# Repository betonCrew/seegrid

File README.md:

seegrid
================================
a floating lighting installation

# Electronics

* nRF24L01+ (2.4GHz)
* xmc1100
* AL8860
* 47µF inductor
* cree rgbw led

## LED

# Mechanics

# Firmware

# Software

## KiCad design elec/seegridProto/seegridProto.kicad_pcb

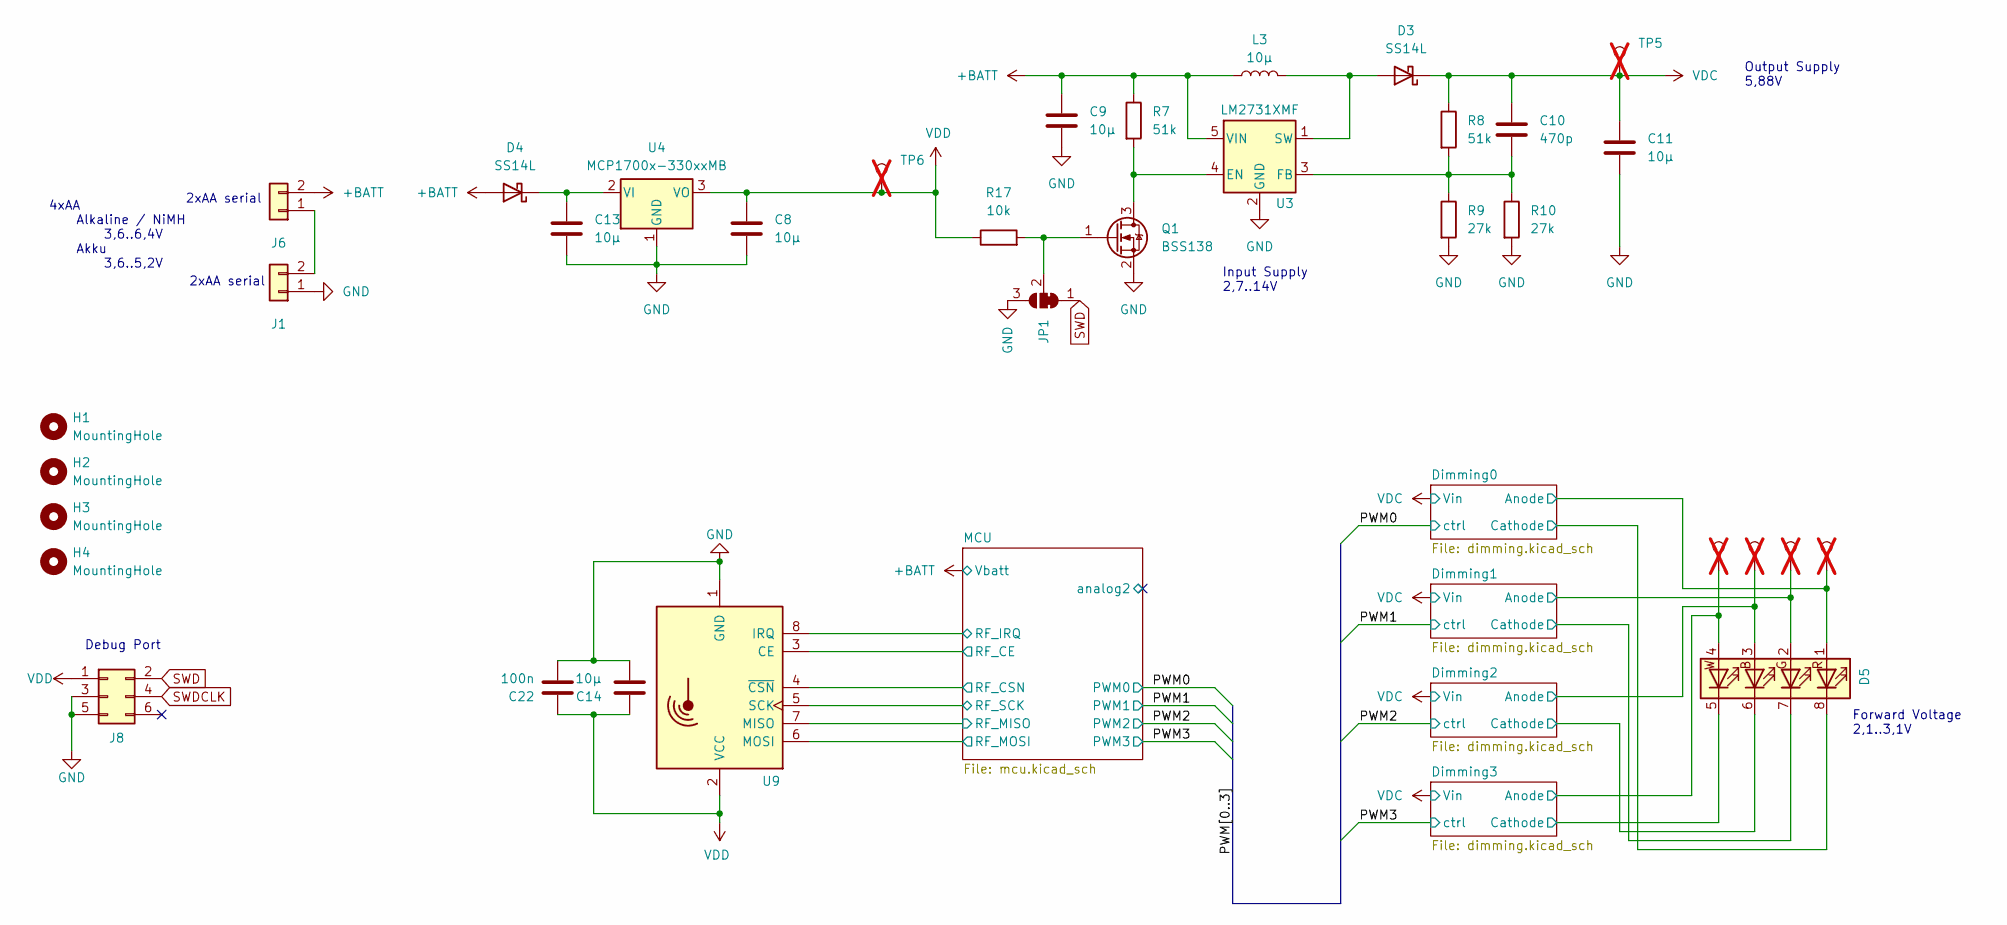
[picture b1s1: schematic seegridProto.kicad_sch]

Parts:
C8, C9, C11, C13, C14: 10µ; C_0603_1608Metric
C10: 470p; C_0603_1608Metric
C22: 100n; C_0603_1608Metric
D3, D4: SS14L; SOD-123FL
D5: CLQ6B-TKW-S1L1R1H1TBB7935AA3; Cree_PLCC8
H1, H2, H3, H4: MountingHole; MountingHole_3.2mm_M3
J1, J6: Conn_01x02; PinSocket_1x02_P2.54mm_Vertical
J8: Conn_02x04_Odd_Even; Tag-Connect_TC2030-IDC-NL_2x03_P1.27mm_Vertical
JP1: SolderJumper_3_Bridged12; SolderJumper-3_P1.3mm_Bridged12_RoundedPad1.0x1.5mm
L3: 10µ; L_7.3x7.3_H4.5
Q1: BSS138; SOT-23
R7, R8: 51k; R_0603_1608Metric
R9, R10: 27k; R_0603_1608Metric
R17: 10k; R_0603_1608Metric
TP1, TP2, TP3, TP4, TP5, TP6: TestPoint; TestPoint_Pad_D1.0mm; not fitted
U3: LM2731XMF; SOT-23-5
U4: MCP1700x-330xxMB; SOT-89-3
U9: NRF24L01_Breakout; nRF24L01_Breakout

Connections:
+BATT: C9.1, D4.2 (A), J6.2, L3.1, R7.1, U3.5 (VIN); also elsewhere on the board
/Dimming0/Anode: D5.1 (RK), TP1.1; also elsewhere on the board
/Dimming0/Cathode: D5.8 (RA); also elsewhere on the board
/Dimming1/Anode: D5.2 (GK), TP2.1; also elsewhere on the board
/Dimming1/Cathode: D5.7 (GA); also elsewhere on the board
/Dimming2/Anode: D5.3 (BK), TP3.1; also elsewhere on the board
/Dimming2/Cathode: D5.6 (BA); also elsewhere on the board
/Dimming3/Anode: D5.4 (BK), TP4.1; also elsewhere on the board
/Dimming3/Cathode: D5.5 (BA); also elsewhere on the board
/MCU/RF_CE: U9.3 (CE); also elsewhere on the board
/MCU/RF_CSN: U9.4 (~CSN); also elsewhere on the board
/MCU/RF_IRQ: U9.8 (IRQ); also elsewhere on the board
/MCU/RF_MISO: U9.7 (MISO); also elsewhere on the board
/MCU/RF_MOSI: U9.6 (MOSI); also elsewhere on the board
/MCU/RF_SCK: U9.5 (SCK); also elsewhere on the board
GND: C8.2, C9.2, C11.2, C13.2, C14.2, C22.2, J1.1, J8.3, J8.5, JP1.3 (B), Q1.2 (S), R9.2, R10.2, U3.2 (GND), U4.1 (GND), U9.1 (GND); also elsewhere on the board
unnamed: D3.2 (A), L3.2, U3.1 (SW)
unnamed: C13.1, D4.1 (K), U4.2 (VI)
unnamed: J1.2, J6.1
unnamed: JP1.2 (C), Q1.1 (G), R17.2
unnamed: Q1.3 (D), R7.2, U3.4 (EN)
unnamed: C10.2, R8.2, R9.1, R10.1, U3.3 (FB)
SWD: J8.2, JP1.1 (A); also elsewhere on the board
SWDCLK: J8.4; also elsewhere on the board
VDC: C10.1, C11.1, D3.1 (K), R8.1, TP5.1; also elsewhere on the board
VDD: C8.1, C14.1, C22.1, J8.1, R17.1, TP6.1, U4.3 (VO), U9.2 (VCC); also elsewhere on the board

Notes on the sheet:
Debug Port
Input Supply 2,7..14V
Forward Voltage 2,1..3,1V
Output Supply 5,88V
2xAA serial
4xAA Alkaline / NiMH 3,6..6,4V Akku 3,6..5,2V

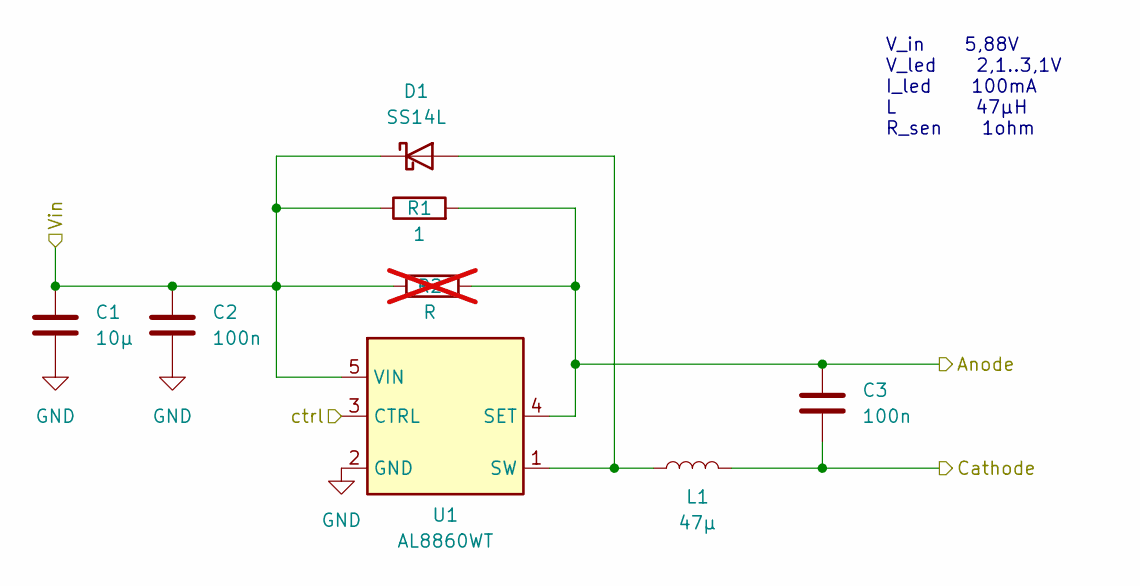
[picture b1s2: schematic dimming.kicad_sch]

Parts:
C1: 10µ; C_0603_1608Metric
C2, C3: 100n; C_0603_1608Metric
D1: SS14L; SOD-123FL
L1: 47µ; L_7.3x7.3_H4.5
R1: 1; R_0603_1608Metric
R2: R; R_0603_1608Metric; not fitted
U1: AL8860WT; TSOT-23-5

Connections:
/Dimming0/Anode: C3.1, R1.2, R2.2, U1.4 (SET); also elsewhere on the board
/Dimming0/Cathode: C3.2, L1.2; also elsewhere on the board
/PWM0: U1.3 (CTRL); also elsewhere on the board
GND: C1.2, C2.2, U1.2 (GND); also elsewhere on the board
unnamed: D1.2 (A), L1.1, U1.1 (SW)
VDC: C1.1, C2.1, D1.1 (K), R1.1, R2.1, U1.5 (VIN); also elsewhere on the board

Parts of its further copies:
C4, C16, C19: 10µ; C_0603_1608Metric
C5, C6, C17, C18, C20, C21: 100n; C_0603_1608Metric
D2, D6, D7: SS14L; SOD-123FL
L2, L4, L5: 47µ; L_7.3x7.3_H4.5
R3, R11, R13: 1; R_0603_1608Metric
R4, R12, R14: R; R_0603_1608Metric; not fitted
U2, U7, U8: AL8860WT; TSOT-23-5

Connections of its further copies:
/Dimming1/Anode: C6.1, R3.2, R4.2, U2.4 (SET); also elsewhere on the board
/Dimming1/Cathode: C6.2, L2.2; also elsewhere on the board
/Dimming2/Anode: C18.1, R11.2, R12.2, U7.4 (SET); also elsewhere on the board
/Dimming2/Cathode: C18.2, L4.2; also elsewhere on the board
/Dimming3/Anode: C21.1, R13.2, R14.2, U8.4 (SET); also elsewhere on the board
/Dimming3/Cathode: C21.2, L5.2; also elsewhere on the board
/PWM1: U2.3 (CTRL); also elsewhere on the board
/PWM2: U7.3 (CTRL); also elsewhere on the board
/PWM3: U8.3 (CTRL); also elsewhere on the board
GND: C4.2, C5.2, C16.2, C17.2, C19.2, C20.2, U2.2 (GND), U7.2 (GND), U8.2 (GND); also elsewhere on the board
unnamed: D2.2 (A), L2.1, U2.1 (SW)
unnamed: D6.2 (A), L4.1, U7.1 (SW)
unnamed: D7.2 (A), L5.1, U8.1 (SW)
VDC: C4.1, C5.1, C16.1, C17.1, C19.1, C20.1, D2.1 (K), D6.1 (K), D7.1 (K), R3.1, R4.1, R11.1, R12.1, R13.1, R14.1, U2.5 (VIN), U7.5 (VIN), U8.5 (VIN); also elsewhere on the board

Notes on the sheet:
V_in 5,88V V_led 2,1..3,1V I_led 100mA L 47µH R_sen 1ohm

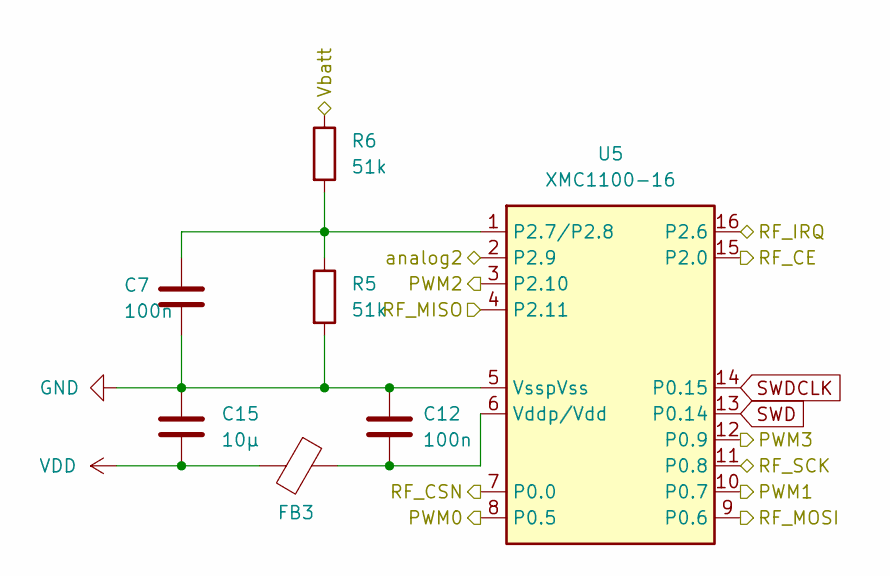
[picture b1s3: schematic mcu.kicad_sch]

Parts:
C7, C12: 100n; C_0603_1608Metric
C15: 10µ; C_0603_1608Metric
FB3: BLM21AG601; L_0805_2012Metric
R5, R6: 51k; R_0603_1608Metric
U5: XMC1100-16; TSSOP-16_4.4x5mm_P0.65mm

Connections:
+BATT: R6.1; also elsewhere on the board
/MCU/RF_CE: U5.15 (P2.0); also elsewhere on the board
/MCU/RF_CSN: U5.7 (P0.0); also elsewhere on the board
/MCU/RF_IRQ: U5.16 (P2.6); also elsewhere on the board
/MCU/RF_MISO: U5.4 (P2.11); also elsewhere on the board
/MCU/RF_MOSI: U5.9 (P0.6); also elsewhere on the board
/MCU/RF_SCK: U5.11 (P0.8); also elsewhere on the board
/MCU/analog2: U5.2 (P2.9)
/PWM0: U5.8 (P0.5); also elsewhere on the board
/PWM1: U5.10 (P0.7); also elsewhere on the board
/PWM2: U5.3 (P2.10); also elsewhere on the board
/PWM3: U5.12 (P0.9); also elsewhere on the board
GND: C7.2, C12.1, C15.1, R5.2, U5.5 (VsspVss); also elsewhere on the board
unnamed: C7.1, R5.1, R6.2, U5.1 (P2.7/P2.8)
unnamed: C12.2, FB3.1, U5.6 (Vddp/Vdd)
SWD: U5.13 (P0.14); also elsewhere on the board
SWDCLK: U5.14 (P0.15); also elsewhere on the board
VDD: C15.2, FB3.2; also elsewhere on the board

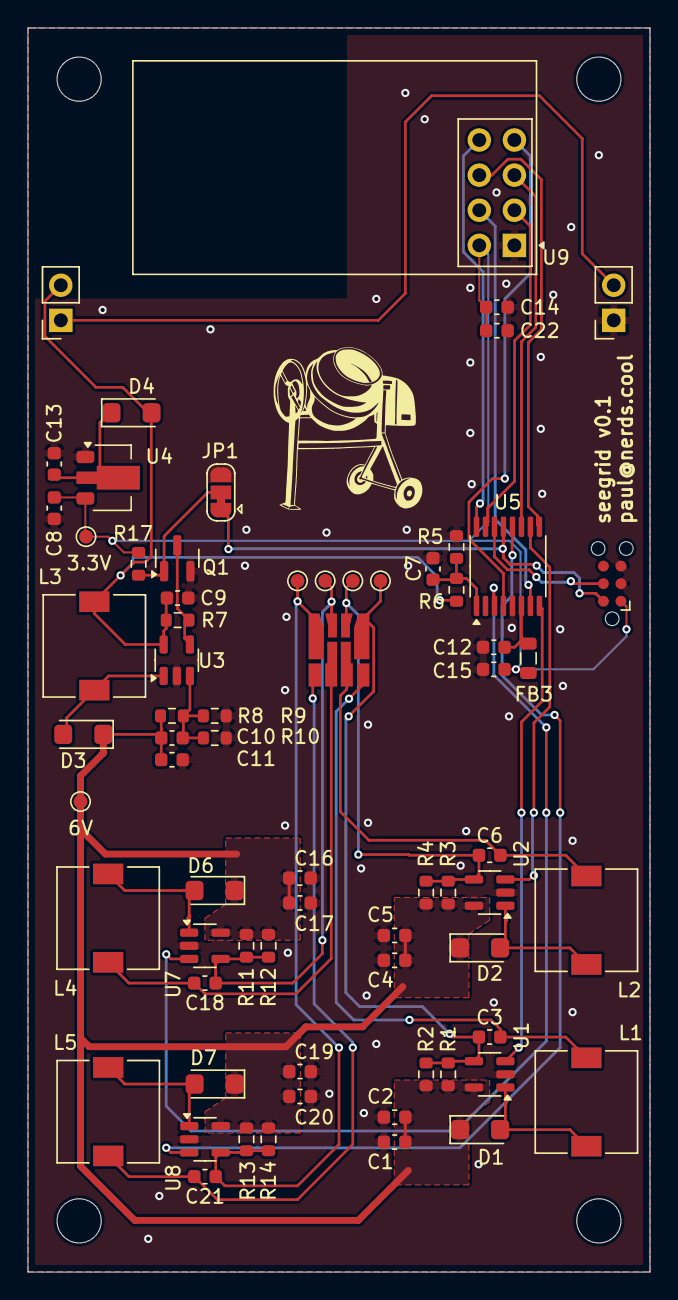
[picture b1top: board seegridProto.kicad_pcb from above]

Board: 2 copper layers, 45.0 x 90.0 mm, 73 parts (0 on the bottom side), 36 nets.

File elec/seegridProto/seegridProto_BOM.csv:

"Reference","Qty","Value","Beschreibung","DNP","Exclude from BOM","Exclude from Board","Footprint","Datasheet","A.Nr_RS","A.URL_DigiKey","A.URL_RS","A.Nr_DigiKey","A.URL_Mouser","A.Nr_Mouser","A.URL_Schukat","A.Nr_Schukat","width","height","length"
"J1,J6","2","Conn_01x02","","","","","Connector_PinSocket_2.54mm:PinSocket_1x02_P2.54mm_Vertical","~","","","","","","","","","","",""
"C2,C3,C5,C6,C7,C12,C17,C18,C20,C21,C22","11","100n","Kerko (X7R),Unpolarized capacitor","","","","Capacitor_SMD:C_0603_1608Metric","~","","","","","","","","","","",""
"U4","1","MCP1700x-330xxMB","250mA Low Quiscent Current LDO, 3.3V output, SOT-89","","","","Package_TO_SOT_SMD:SOT-89-3","http://ww1.microchip.com/downloads/en/DeviceDoc/20001826D.pdf","","","","","","","","","","",""
"JP1","1","SolderJumper_3_Bridged12","3-pole Solder Jumper, pins 1+2 closed/bridged","","Von Bauteilliste ausgeschlossen","","Jumper:SolderJumper-3_P1.3mm_Bridged12_RoundedPad1.0x1.5mm","~","","","","","","","","","","",""
"D1,D2,D3,D4,D6,D7","6","SS14L","40V 1A Schottky Diode, SMA","","","","LED_Lib:SOD-123FL","https://www.vishay.com/docs/88746/ss12.pdf","","","","","","","","","","",""
"U1,U2,U7,U8","4","AL8860WT","40V 1.5A Constant Current Buck LED Driver IC, TSOT-23-5","","","","Package_TO_SOT_SMD:TSOT-23-5","https://www.diodes.com/assets/Datasheets/AL8860.pdf","","","","","","","","","","",""
"Q1","1","BSS138","50V Vds, 0.22A Id, N-Channel MOSFET, SOT-23","","","","Package_TO_SOT_SMD:SOT-23","https://www.onsemi.com/pub/Collateral/BSS138-D.PDF","","","","","","","","","","",""
"FB3","1","BLM21AG601","Ferrite bead","","","","Inductor_SMD:L_0805_2012Metric","~","","","","","","","","","","",""
"J8","1","Conn_02x04_Odd_Even","Generic connector, double row, 02x03, odd/even pin numbering scheme (row 1 odd numbers, row 2 even numbers), script generated (kicad-library-utils/schlib/autogen/connector/)","","","","Connector:Tag-Connect_TC2030-IDC-NL_2x03_P1.27mm_Vertical","~","","","","","","","","","","",""
"L1,L2,L4,L5","4","47µ","Inductor","","","","Inductor_SMD:L_7.3x7.3_H4.5","~","","","","","","","","","","",""
"L3","1","10µ","Inductor","","","","Inductor_SMD:L_7.3x7.3_H4.5","~","","","","","","","","","","",""
"U3","1","LM2731XMF","LM27313, 1.8A, 22Vout Boost Voltage Regulator, 1.6MHz Frequency, SOT-23-5","","","","Package_TO_SOT_SMD:SOT-23-5","http://www.ti.com/lit/ds/symlink/lm2731.pdf","","","","","","","","","","",""
"H1,H2,H3,H4","4","MountingHole","Mounting Hole without connection","","Von Bauteilliste ausgeschlossen","","MountingHole:MountingHole_3.2mm_M3","~","","","","","","","","","","",""
"R1,R3,R11,R13","4","1","Resistor","","","","Resistor_SMD:R_0603_1608Metric","~","","","","","","","","","","",""
"R2,R4,R12,R14","4","R","Resistor","Nicht bestücken","","","Resistor_SMD:R_0603_1608Metric","~","","","","","","","","","","",""
"R5,R6,R7,R8","4","51k","Resistor","","","","Resistor_SMD:R_0603_1608Metric","~","","","","","","","","","","",""
"R9,R10","2","27k","Resistor","","","","Resistor_SMD:R_0603_1608Metric","~","","","","","","","","","","",""
"R17","1","10k","Resistor","","","","Resistor_SMD:R_0603_1608Metric","~","","","","","","","","","","",""
"D5","1","CLQ6B-TKW-S1L1R1H1TBB7935AA3","RGB LED, 6 pin package","","","","LED_Lib:Cree_PLCC8","https://eu.mouser.com/ProductDetail/Cree-LED/CLQ6B-TKW-S1L1R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","","","","","","","","","","",""
"TP1,TP2,TP3,TP4,TP5,TP6","6","TestPoint","test point","Nicht bestücken","","","TestPoint:TestPoint_Pad_D1.0mm","~","","","","","","","","","","",""
"U5","1","XMC1100-16","TSSOP-16","","","","Package_SO:TSSOP-16_4.4x5mm_P0.65mm","","","","","","","","","","","",""
"U9","1","NRF24L01_Breakout","Ultra low power 2.4GHz RF Transceiver, Carrier PCB","","","","RF_Module:nRF24L01_Breakout","http://www.nordicsemi.com/eng/content/download/2730/34105/fi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","","","","","","","","","","",""
"C1,C4,C8,C9,C11,C13,C14,C15,C16,C19","10","10µ","Unpolarized capacitor","","","","Capacitor_SMD:C_0603_1608Metric","~","","","","","","","","","","",""
"C10","1","470p","Unpolarized capacitor","","","","Capacitor_SMD:C_0603_1608Metric","~","","","","","","","","","","",""

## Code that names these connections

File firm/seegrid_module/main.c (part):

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        }
    };

    // TODO curr SWD Pins, change that!
    // boostCon_t boost = {
    //     .port = BOOST_PORT,
    //     .pin = BOOST_PIN,
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        .spiSelo = XMC_SPI_CH_SLAVE_SELECT_0,
        .irqN = RF_IRQ_OGU_IRQN,
        .irqPort = RF_IRQ_PORT,
        .irqPin = RF_IRQ_PIN,
        .cePort = RF_CE_PORT,
        .cePin = RF_CE_PIN,
        .mode = FIXTURE,
        .data = universe,
    };
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
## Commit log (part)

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2025-10-22 picked up project
2025-10-22 amend

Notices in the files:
firm/seegrid_module/main.c:
Copyright (c) 2015-2021, Infineon Technologies AG
All rights reserved.
